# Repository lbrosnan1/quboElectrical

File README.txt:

Guys I have no idea what I'm doing here so if you have any suggestions lmk -Liam

Rules:

1) Only commit changes to the card you are meant to be working on
2) leave helpful commit messages
3) you don't need to follow the naming scheme because I'm pretty sure we can just see the date the latest change was
4) Put cool silkscreen on your boards

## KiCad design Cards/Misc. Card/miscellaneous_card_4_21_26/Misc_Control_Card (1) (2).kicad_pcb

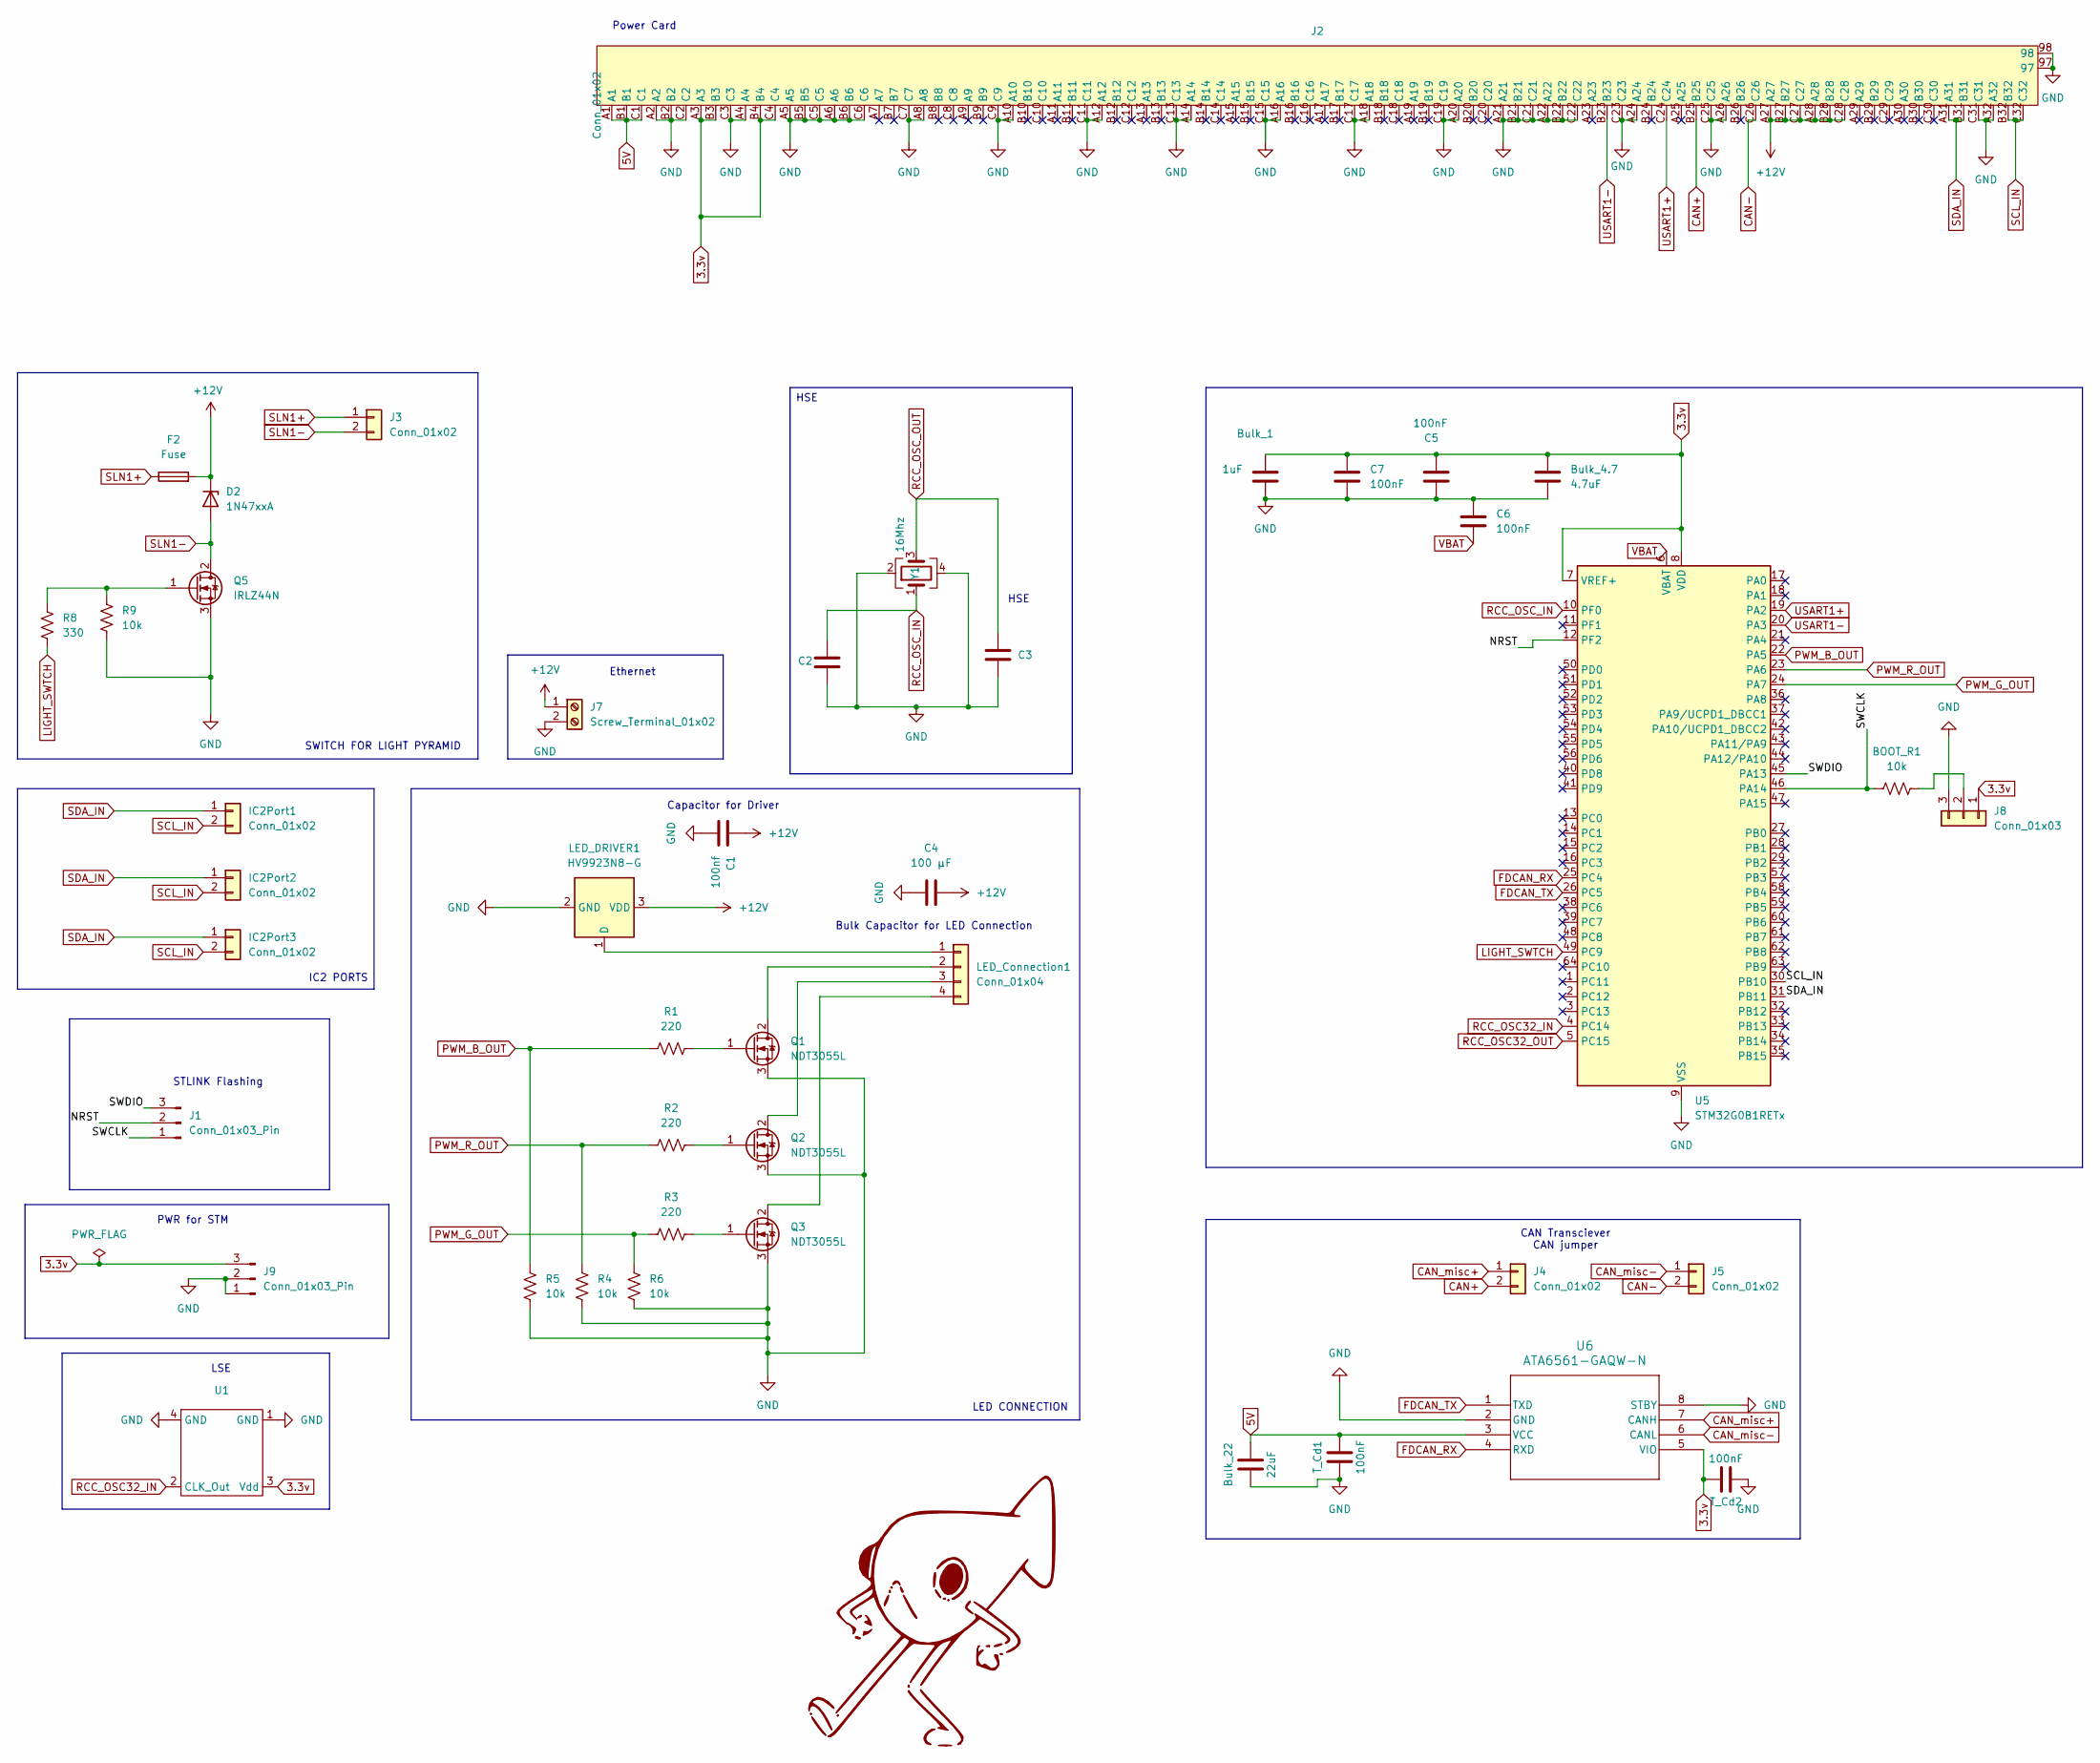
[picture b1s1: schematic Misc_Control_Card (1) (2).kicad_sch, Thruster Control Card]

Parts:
BOOT_R1: 10k; R_0805_2012Metric_Pad1.20x1.40mm_HandSolder
Bulk_1: 1uF; C_0805_2012Metric_Pad1.18x1.45mm_HandSolder
Bulk_4.7: 4.7uF; C_0805_2012Metric_Pad1.18x1.45mm_HandSolder
Bulk_22: 22uF; C_0805_2012Metric_Pad1.18x1.45mm_HandSolder
C1: 100nf; C_0805_2012Metric_Pad1.18x1.45mm_HandSolder
C2, C3: 10pF; C_0805_2012Metric_Pad1.18x1.45mm_HandSolder
C4: 100 µF; C_0805_2012Metric_Pad1.18x1.45mm_HandSolder
C5, C6, C7: 100nF; C_0805_2012Metric_Pad1.18x1.45mm_HandSolder
D2: 1N47xxA; D_DO-41_SOD81_P10.16mm_Horizontal
F2: Fuse; Fuseholder_Littelfuse_Nano2_154x
IC2Port1, IC2Port2, IC2Port3: Conn_01x02; JST_PH_B2B-PH-K_1x02_P2.00mm_Vertical
J1, J9: Conn_01x03_Pin; PinHeader_1x03_P2.54mm_Vertical
J2: Conn_01x02; 6509475
J3: Conn_01x02; JST_PH_B2B-PH-K_1x02_P2.00mm_Vertical
J4, J5: Conn_01x02; PinHeader_1x02_P2.54mm_Vertical
J7: Screw_Terminal_01x02; screw_junc_254_2by1
J8: Conn_01x03; slide_switch_EGER1218_Thruster
LED_Connection1: Conn_01x04; JST_EH_B4B-EH-A_1x04_P2.50mm_Vertical
LED_DRIVER1: HV9923N8-G; SOT-89-3
Q1, Q2, Q3: NDT3055L; SOT-223-3_TabPin2
Q5: IRLZ44N; TO-220-3_Vertical
R1, R2, R3: 220; R_0805_2012Metric_Pad1.20x1.40mm_HandSolder
R4, R5, R6, R9: 10k; R_0805_2012Metric_Pad1.20x1.40mm_HandSolder
R8: 330; R_0805_2012Metric_Pad1.20x1.40mm_HandSolder
T_Cd1, T_Cd2: 100nF; C_0805_2012Metric_Pad1.18x1.45mm_HandSolder
U1: SiT1552
U5: STM32G0B1RETx; LQFP-64_10x10mm_P0.5mm
U6: ATA6561-GAQW-N; SOIC8_4P9X3P9MC_MCH
Y1: 16Mhz; Crystal_SMD_3225-4Pin_3.2x2.5mm_HandSoldering

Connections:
3.3v: Bulk_1.2, Bulk_4.7.1, C5.1, C7.1, J1.A3, J1.B3, J1.B4, J1.C4, J2.A3, J2.B3, J2.B4, J2.C4, J8.1, J9.3, T_Cd2.1, U1.3 (Vdd), U5.7 (VREF+), U5.8 (VDD), U6.5 (VIO); also elsewhere on the board
5V: Bulk_22.1, J2.A1, J2.B1, J2.C1, T_Cd1.1, U6.3 (VCC)
+12V: C1.1, C4.1, D2.1 (K), F2.2, J1.A27, J1.A28, J1.B27, J1.B28, J1.C27, J1.C28, J2.A27, J2.A28, J2.B27, J2.B28, J2.C27, J2.C28, J7.1, LED_DRIVER1.3 (VDD); also elsewhere on the board
/NRST: J1.2, U5.12 (PF2)
/SWCLK: BOOT_R1.1, J1.1, U5.46 (PA14)
/SWDIO: J1.3, U5.45 (PA13)
CAN+: J2.B25, J4.2
CAN-: J2.C26, J5.2
CAN_misc+: J4.1, U6.7 (CANH)
CAN_misc-: J5.1, U6.6 (CANL)
FDCAN_RX: U5.25 (PC4), U6.4 (RXD)
FDCAN_TX: U5.26 (PC5), U6.1 (TXD)
GND: Bulk_1.1, Bulk_4.7.2, Bulk_22.2, C1.2, C2.2, C3.2, C4.2, C5.2, C6.1, C7.2, J1.97, J1.98, J1.A2, J1.A4, J1.A5, J1.A6, J1.A8, J1.A10, J1.A12, J1.A14, J1.A16, J1.A18, J1.A20, J1.A21, J1.A22, J1.A24, J1.A26, J1.A32, J1.B2, J1.B5, J1.B6, J1.B21, J1.B22, J1.C2, J1.C3, J1.C5, J1.C6, J1.C7, J1.C9, J1.C11, J1.C13, J1.C15, J1.C17, J1.C19, J1.C21, J1.C22, J1.C23, J1.C25, J1.C31, J2.97, J2.98, J2.A2, J2.A4, J2.A5, J2.A6, J2.A8, J2.A10, J2.A12, J2.A14, J2.A16, J2.A18, J2.A20, J2.A21, J2.A22, J2.A24, J2.A26, J2.A32, J2.B2, J2.B5, J2.B6, J2.B21, J2.B22, J2.C2, J2.C3, J2.C5, J2.C6, J2.C7, J2.C9, J2.C11, J2.C13, J2.C15, J2.C17, J2.C19, J2.C21, J2.C22, J2.C23, J2.C25, J2.C31, J7.2, J8.3, J9.1, J9.2, LED_DRIVER1.2 (GND), Q1.3 (S), Q2.3 (S), Q3.3 (S), Q5.3 (S), R4.1, R5.1, R6.1, R9.2, T_Cd1.2, T_Cd2.2, U1.1 (GND), U1.4 (GND), U5.9 (VSS), U6.2 (GND), U6.8 (STBY), Y1.2, Y1.4; also elsewhere on the board
LIGHT_SWTCH: R8.1, U5.49 (PC9)
unnamed: BOOT_R1.2, J8.2
unnamed 15: LED_Connection1.1, LED_DRIVER1.1 (D); also elsewhere on the board
unnamed 16: LED_Connection1.2, Q1.2 (D); also elsewhere on the board
unnamed 17: LED_Connection1.3, Q2.2 (D); also elsewhere on the board
unnamed 18: LED_Connection1.4, Q3.2 (D); also elsewhere on the board
unnamed: Q1.1 (G), R1.2
unnamed: Q2.1 (G), R2.2
unnamed: Q3.1 (G), R3.2
unnamed 22: Q5.1 (G), R8.2, R9.1; also elsewhere on the board
PWM_B_OUT: R1.1, R5.2, U5.22 (PA5)
PWM_G_OUT: R3.1, R6.2, U5.24 (PA7)
PWM_R_OUT: R2.1, R4.2, U5.23 (PA6)
RCC_OSC32_IN: U1.2 (CLK_Out), U5.4 (PC14)
RCC_OSC32_OUT: U5.5 (PC15)
RCC_OSC_IN: C2.1, U5.10 (PF0), Y1.1
RCC_OSC_OUT: C3.1, Y1.3
SCL_IN: IC2Port1.2, IC2Port2.2, IC2Port3.2, J2.B32, J2.C32, U5.30 (PB10)
SDA_IN: IC2Port1.1, IC2Port2.1, IC2Port3.1, J2.A31, J2.B31, U5.31 (PB11)
SLN1+: F2.1, J3.1
SLN1-: D2.2 (A), J3.2, Q5.2 (D); also elsewhere on the board
USART1+: J2.C24, U5.19 (PA2)
USART1-: J2.B23, U5.20 (PA3)
VBAT: C6.2, U5.6 (VBAT)

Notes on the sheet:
Bulk Capacitor for LED Connection
Power Card
LSE
IC2 PORTS
Capacitor for Driver
STLINK Flashing
PWR for STM
CAN Transciever CAN jumper
SWITCH FOR LIGHT PYRAMID
HSE
LED CONNECTION
Ethernet
HSE

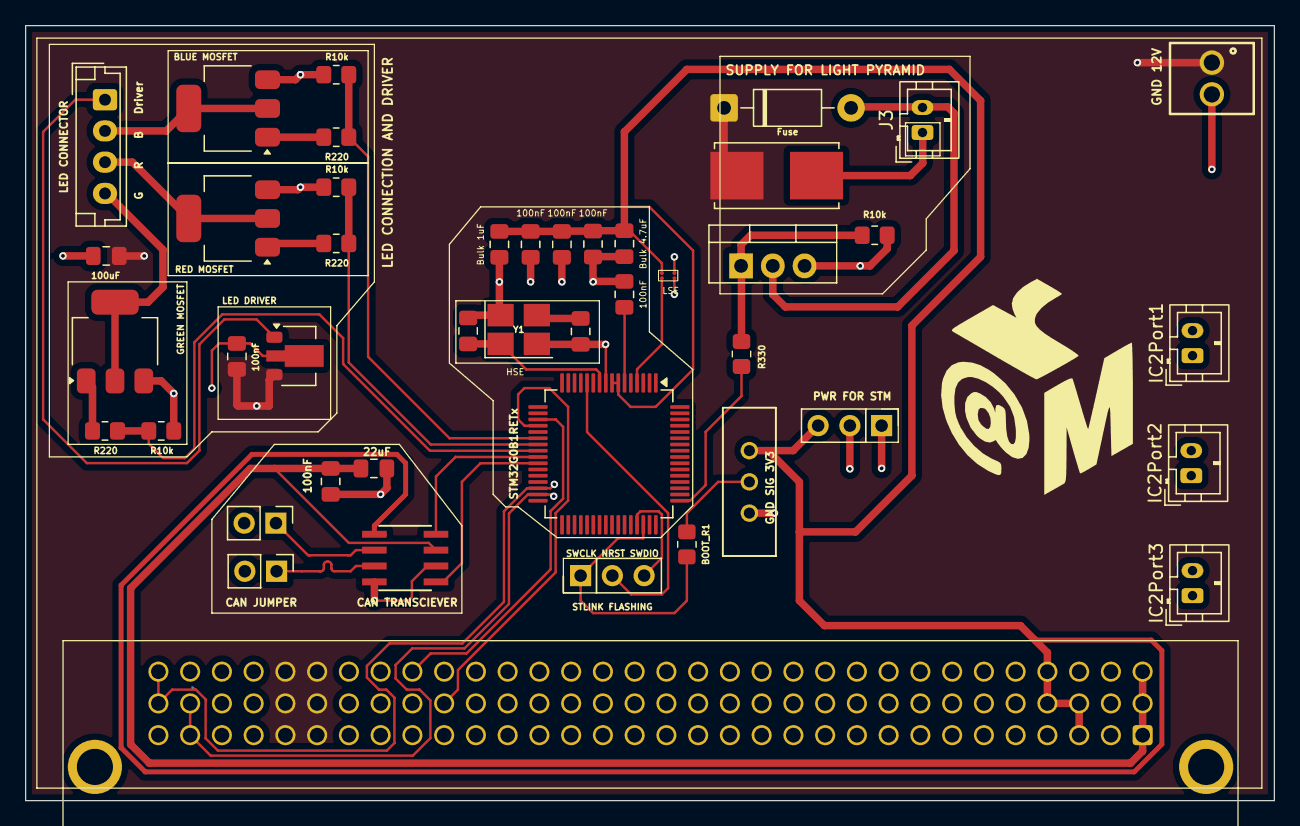
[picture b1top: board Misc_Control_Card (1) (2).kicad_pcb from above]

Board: 4 copper layers, 99.9 x 62.0 mm, 44 parts (0 on the bottom side), 36 nets.

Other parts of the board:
Bulk 4.7uF: 4.7uF; C_0805_2012Metric_Pad1.18x1.45mm_HandSolder
Fuse: 1N47xxA; D_DO-41_SOD81_P10.16mm_Horizontal
LED Connection: Conn_01x04; JST_EH_B4B-EH-A_1x04_P2.50mm_Vertical
R10k: 10k; R_0805_2012Metric_Pad1.20x1.40mm_HandSolder

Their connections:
3.3v: Bulk 4.7uF.1; also elsewhere on the board
+12V: Fuse.1 (K); also elsewhere on the board
GND: Bulk 4.7uF.2, R10k.2; also elsewhere on the board
unnamed 15: LED Connection.1; also elsewhere on the board
unnamed 16: LED Connection.2; also elsewhere on the board
unnamed 17: LED Connection.3; also elsewhere on the board
unnamed 18: LED Connection.4; also elsewhere on the board
unnamed 22: R10k.1; also elsewhere on the board
SLN1-: Fuse.2 (A); also elsewhere on the board

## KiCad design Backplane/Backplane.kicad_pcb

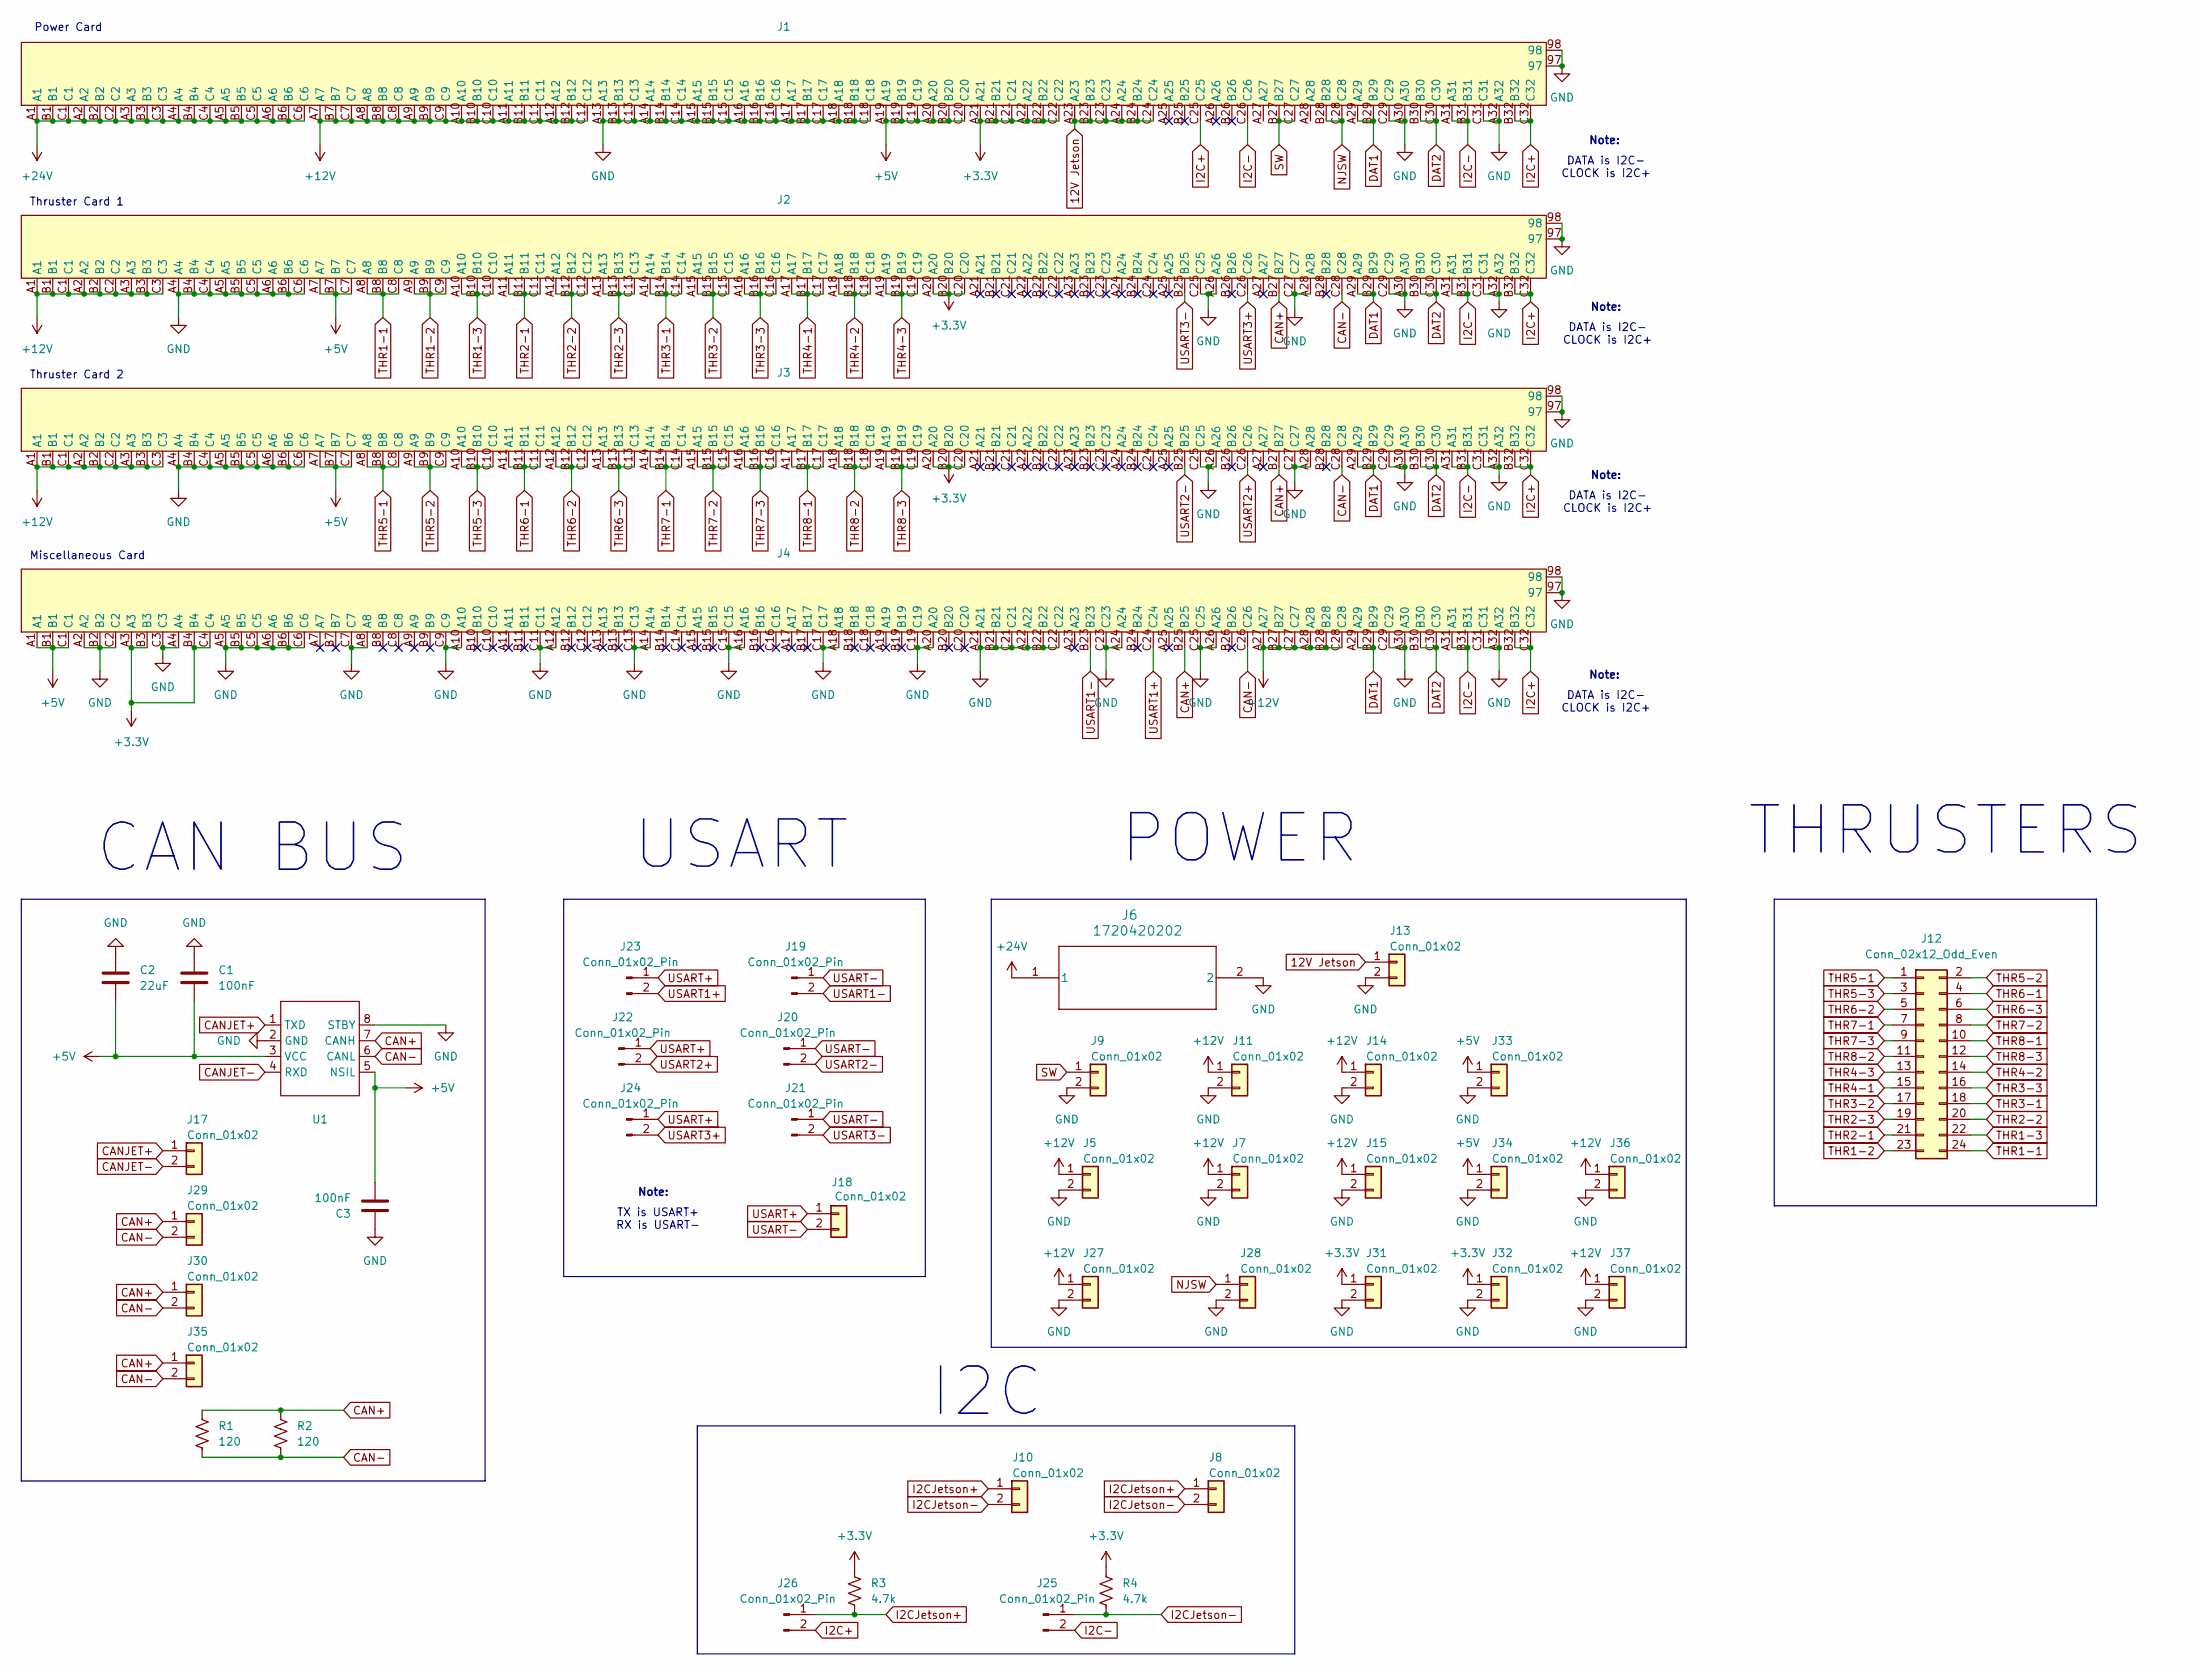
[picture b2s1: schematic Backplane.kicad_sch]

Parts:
C1, C3: 100nF; C_0805_2012Metric
C2: 22uF; C_0805_2012Metric
J1, J2, J3, J4: CONN_650470-5_TYC
J5, J7, J8, J9, J10, J11, J13, J14, J15, J17, J18, J27, J28, J29, J30, J31, J32, J33, J34, J35, J36, J37: Conn_01x02; JST_PH_B2B-PH-K_1x02_P2.00mm_Vertical
J6: 1720420202; SUPERSABRE_2CIRCUIT
J12: Conn_02x12_Odd_Even; Molex_Mini-Fit_Jr_5566-24A_2x12_P4.20mm_Vertical
J19, J20, J21, J22, J23, J24, J25, J26: Conn_01x02_Pin; PinHeader_1x02_P2.54mm_Vertical
R1, R2: 120; R_0805_2012Metric
R3, R4: 4.7k; R_0805_2012Metric
U1: SOIC-8_3.9x4.9mm_P1.27mm

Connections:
12V Jetson: J1.A23, J1.A24, J1.B23, J1.B24, J1.C23, J1.C24, J13.1
+3.3V: J1.A21, J1.A22, J1.B21, J1.B22, J1.C21, J1.C22, J2.A20, J2.B20, J2.C20, J3.A20, J3.B20, J3.C20, J4.A3, J4.B3, J4.B4, J4.C4, J31.1, J32.1, R3.1, R4.1
+5V: C1.2, C2.2, C3.2, J1.A19, J1.A20, J1.B19, J1.B20, J1.C19, J1.C20, J2.A7, J2.B7, J2.C7, J3.A7, J3.B7, J3.C7, J4.A1, J4.B1, J4.C1, J33.1, J34.1, U1.3 (VCC), U1.5 (NSIL)
+12V: J1.A7, J1.A8, J1.A9, J1.A10, J1.A11, J1.A12, J1.B7, J1.B8, J1.B9, J1.B10, J1.B11, J1.B12, J1.C7, J1.C8, J1.C9, J1.C10, J1.C11, J1.C12, J2.A1, J2.A2, J2.A3, J2.B1, J2.B2, J2.B3, J2.C1, J2.C2, J2.C3, J3.A1, J3.A2, J3.A3, J3.B1, J3.B2, J3.B3, J3.C1, J3.C2, J3.C3, J4.A27, J4.A28, J4.B27, J4.B28, J4.C27, J4.C28, J5.1, J7.1, J11.1, J14.1, J15.1, J27.1, J36.1, J37.1
+24V: J1.A1, J1.A2, J1.A3, J1.A4, J1.A5, J1.A6, J1.B1, J1.B2, J1.B3, J1.B4, J1.B5, J1.B6, J1.C1, J1.C2, J1.C3, J1.C4, J1.C5, J1.C6, J6.1
CAN+: J2.B27, J3.B27, J4.B25, J29.1, J30.1, J35.1, R1.1, R2.1, U1.7 (CANH)
CAN-: J2.C28, J3.C28, J4.C26, J29.2, J30.2, J35.2, R1.2, R2.2, U1.6 (CANL)
CANJET+: J17.1, U1.1 (TXD)
CANJET-: J17.2, U1.4 (RXD)
DAT1: J1.A29, J1.B29, J2.A29, J2.B29, J3.A29, J3.B29, J4.A29, J4.B29
DAT2: J1.B30, J1.C30, J2.B30, J2.C30, J3.B30, J3.C30, J4.B30, J4.C30
GND: C1.1, C2.1, C3.1, J1.97, J1.98, J1.A13, J1.A14, J1.A15, J1.A16, J1.A17, J1.A18, J1.A30, J1.A32, J1.B13, J1.B14, J1.B15, J1.B16, J1.B17, J1.B18, J1.C13, J1.C14, J1.C15, J1.C16, J1.C17, J1.C18, J1.C29, J1.C31, J2.97, J2.98, J2.A4, J2.A5, J2.A6, J2.A26, J2.A28, J2.A30, J2.A32, J2.B4, J2.B5, J2.B6, J2.C4, J2.C5, J2.C6, J2.C25, J2.C27, J2.C29, J2.C31, J3.97, J3.98, J3.A4, J3.A5, J3.A6, J3.A26, J3.A28, J3.A30, J3.A32, J3.B4, J3.B5, J3.B6, J3.C4, J3.C5, J3.C6, J3.C25, J3.C27, J3.C29, J3.C31, J4.97, J4.98, J4.A2, J4.A4, J4.A5, J4.A6, J4.A8, J4.A10, J4.A12, J4.A14, J4.A16, J4.A18, J4.A20, J4.A21, J4.A22, J4.A24, J4.A26, J4.A30, J4.A32, J4.B2, J4.B5, J4.B6, J4.B21, J4.B22, J4.C2, J4.C3, J4.C5, J4.C6, J4.C7, J4.C9, J4.C11, J4.C13, J4.C15, J4.C17, J4.C19, J4.C21, J4.C22, J4.C23, J4.C25, J4.C29, J4.C31, J5.2, J6.2, J7.2, J9.2, J11.2, J13.2, J14.2, J15.2, J27.2, J28.2, J31.2, J32.2, J33.2, J34.2, J36.2, J37.2, U1.2 (GND), U1.8 (STBY)
I2C+: J1.B32, J1.C25, J1.C32, J2.B32, J2.C32, J3.B32, J3.C32, J4.B32, J4.C32, J26.2
I2C-: J1.A31, J1.B31, J1.C26, J2.A31, J2.B31, J3.A31, J3.B31, J4.A31, J4.B31, J25.2
I2CJetson+: J8.1, J10.1, J26.1, R3.2
I2CJetson-: J8.2, J10.2, J25.1, R4.2
NJSW: J1.B28, J1.C28, J28.1
SW: J1.B27, J1.C27, J9.1
THR1-1: J2.A8, J2.B8, J2.C8, J12.24
THR1-2: J2.A9, J2.B9, J2.C9, J12.23
THR1-3: J2.A10, J2.B10, J2.C10, J12.22
THR2-1: J2.A11, J2.B11, J2.C11, J12.21
THR2-2: J2.A12, J2.B12, J2.C12, J12.20
THR2-3: J2.A13, J2.B13, J2.C13, J12.19
THR3-1: J2.A14, J2.B14, J2.C14, J12.18
THR3-2: J2.A15, J2.B15, J2.C15, J12.17
THR3-3: J2.A16, J2.B16, J2.C16, J12.16
THR4-1: J2.A17, J2.B17, J2.C17, J12.15
THR4-2: J2.A18, J2.B18, J2.C18, J12.14
THR4-3: J2.A19, J2.B19, J2.C19, J12.13
THR5-1: J3.A8, J3.B8, J3.C8, J12.1
THR5-2: J3.A9, J3.B9, J3.C9, J12.2
THR5-3: J3.A10, J3.B10, J3.C10, J12.3
THR6-1: J3.A11, J3.B11, J3.C11, J12.4
THR6-2: J3.A12, J3.B12, J3.C12, J12.5
THR6-3: J3.A13, J3.B13, J3.C13, J12.6
THR7-1: J3.A14, J3.B14, J3.C14, J12.7
THR7-2: J3.A15, J3.B15, J3.C15, J12.8
THR7-3: J3.A16, J3.B16, J3.C16, J12.9
THR8-1: J3.A17, J3.B17, J3.C17, J12.10
THR8-2: J3.A18, J3.B18, J3.C18, J12.11
THR8-3: J3.A19, J3.B19, J3.C19, J12.12
USART1+: J4.C24, J23.2
USART1-: J4.B23, J19.2
USART2+: J3.C26, J22.2
USART2-: J3.B25, J20.2
USART3+: J2.C26, J24.2
USART3-: J2.B25, J21.2
USART+: J18.1, J22.1, J23.1, J24.1
USART-: J18.2, J19.1, J20.1, J21.1

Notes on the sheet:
I2C
Note:
POWER
Thruster Card 1
DATA is I2C- CLOCK is I2C+
Miscellaneous Card
THRUSTERS
Power Card
USART
Thruster Card 2
CAN BUS
TX is USART+ RX is USART-

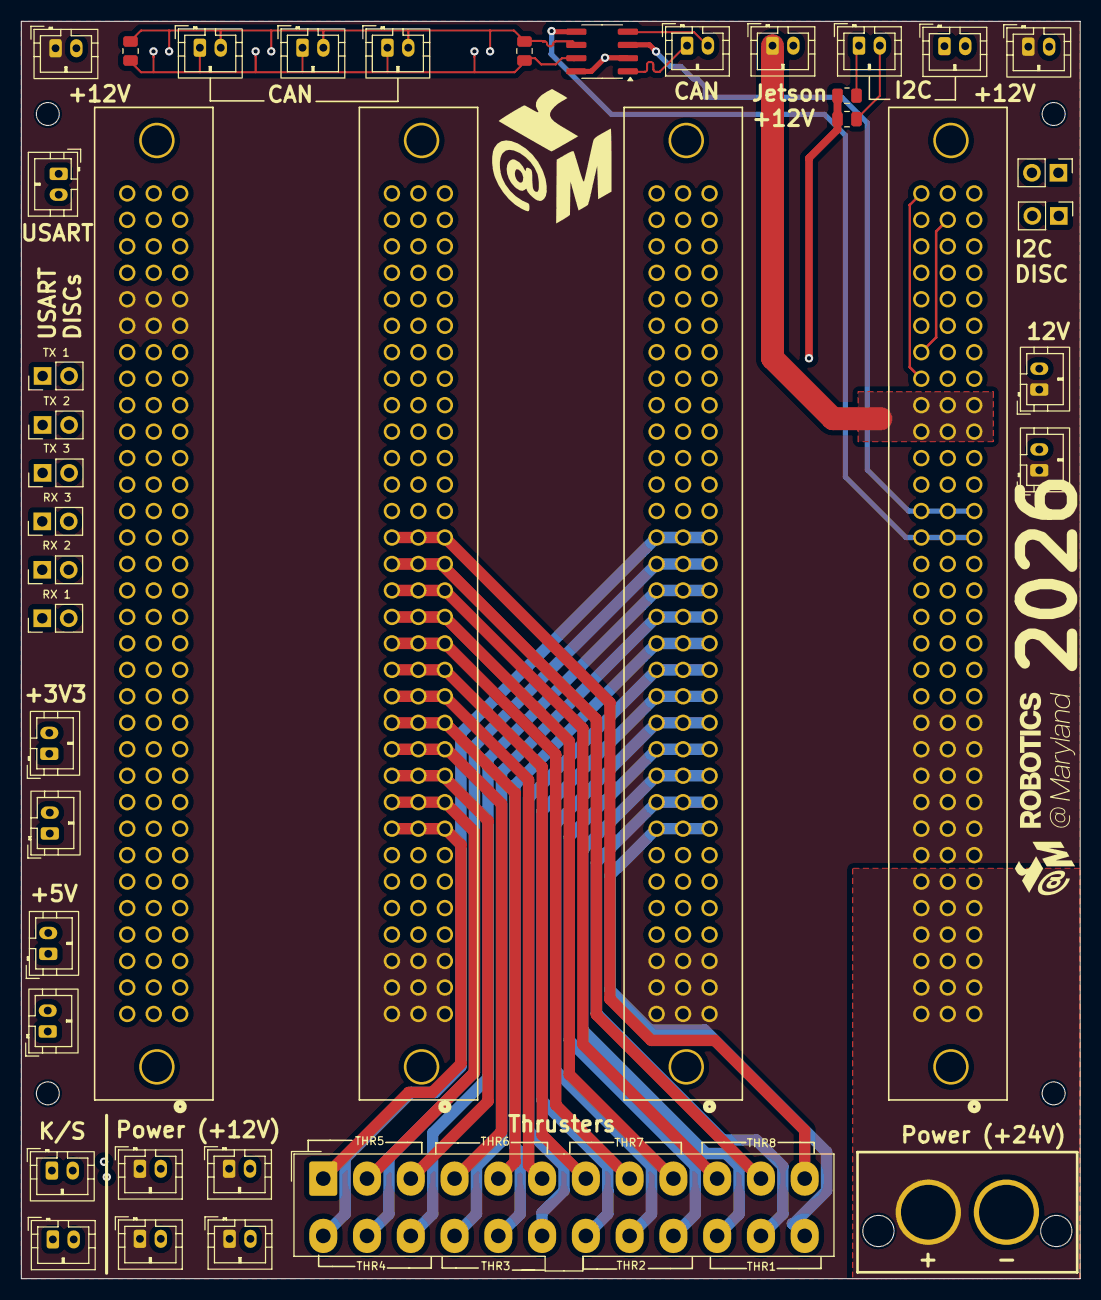
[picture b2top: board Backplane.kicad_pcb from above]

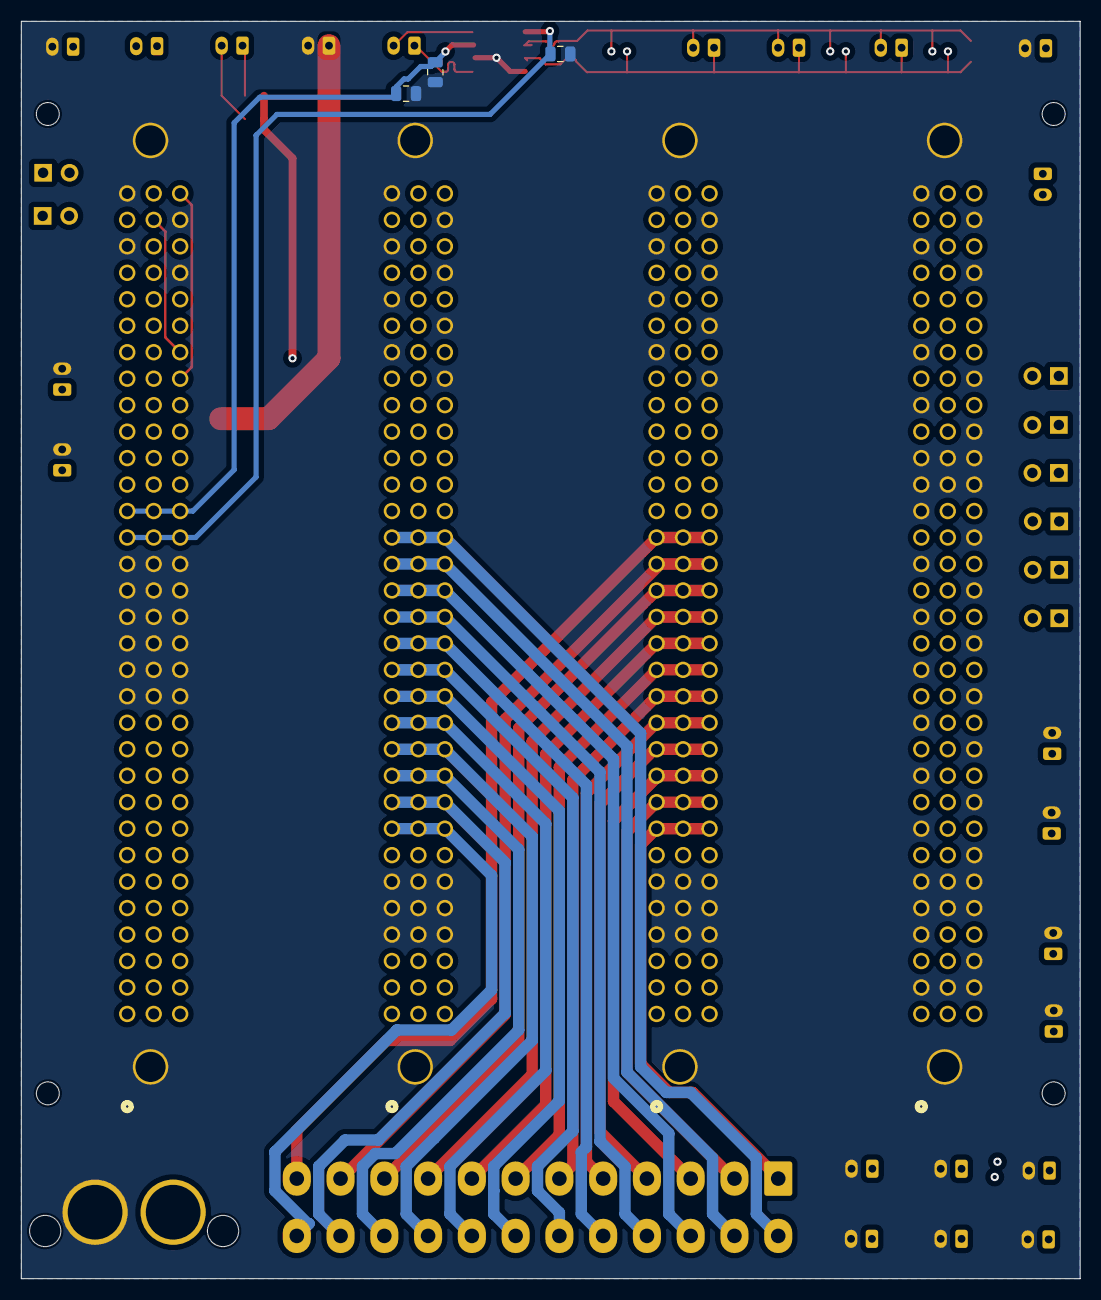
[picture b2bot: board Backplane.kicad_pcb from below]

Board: 4 copper layers, 101.6 x 120.6 mm, 44 parts (3 on the bottom side), 50 nets.

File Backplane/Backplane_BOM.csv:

"Id";"Designator";"Footprint";"Quantity";"Designation";"Supplier and ref";
1;"J11,J33,J17,J5,J18,J13,J8,J15,J29,J31,J34,J14,J9,J35,J28,J7,J37,J10,J32,J30,J27,J36";"JST_PH_B2B-PH-K_1x02_P2.00mm_Vertical";22;"Conn_01x02";;;
2;"J24,J25,J26,J21,J23,J20,J22,J19";"PinHeader_1x02_P2.54mm_Vertical";8;"Conn_01x02_Pin";;;
3;"R2,R1";"R_0805_2012Metric";2;"120";;;
4;"R4,R3";"R_0805_2012Metric";2;"4.7k";;;
5;"J3,J2,J1,J4";"CONN_650470-5_TYC";4;"~";;;
6;"U1";"SOIC-8_3.9x4.9mm_P1.27mm";1;"~";;;
7;"J6";"SUPERSABRE_2CIRCUIT";1;"1720420202";;;
8;"J12";"Molex_Mini-Fit_Jr_5566-24A_2x12_P4.20mm_Vertical";1;"Conn_02x12_Odd_Even";;;
9;"C2";"C_0805_2012Metric";1;"22uF";;;
10;"C1,C3";"C_0805_2012Metric";2;"100nF";;;
